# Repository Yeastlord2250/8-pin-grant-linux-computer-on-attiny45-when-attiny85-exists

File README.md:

# 8-pin-grant-linux-computer-on-attiny45-when-attiny85-exists
A stupid attempt at making a pcb with only 8-pin components using kicad, something I have never done, and also getting linux on an attiny 45, even though I could choose an attiny 85 instead.

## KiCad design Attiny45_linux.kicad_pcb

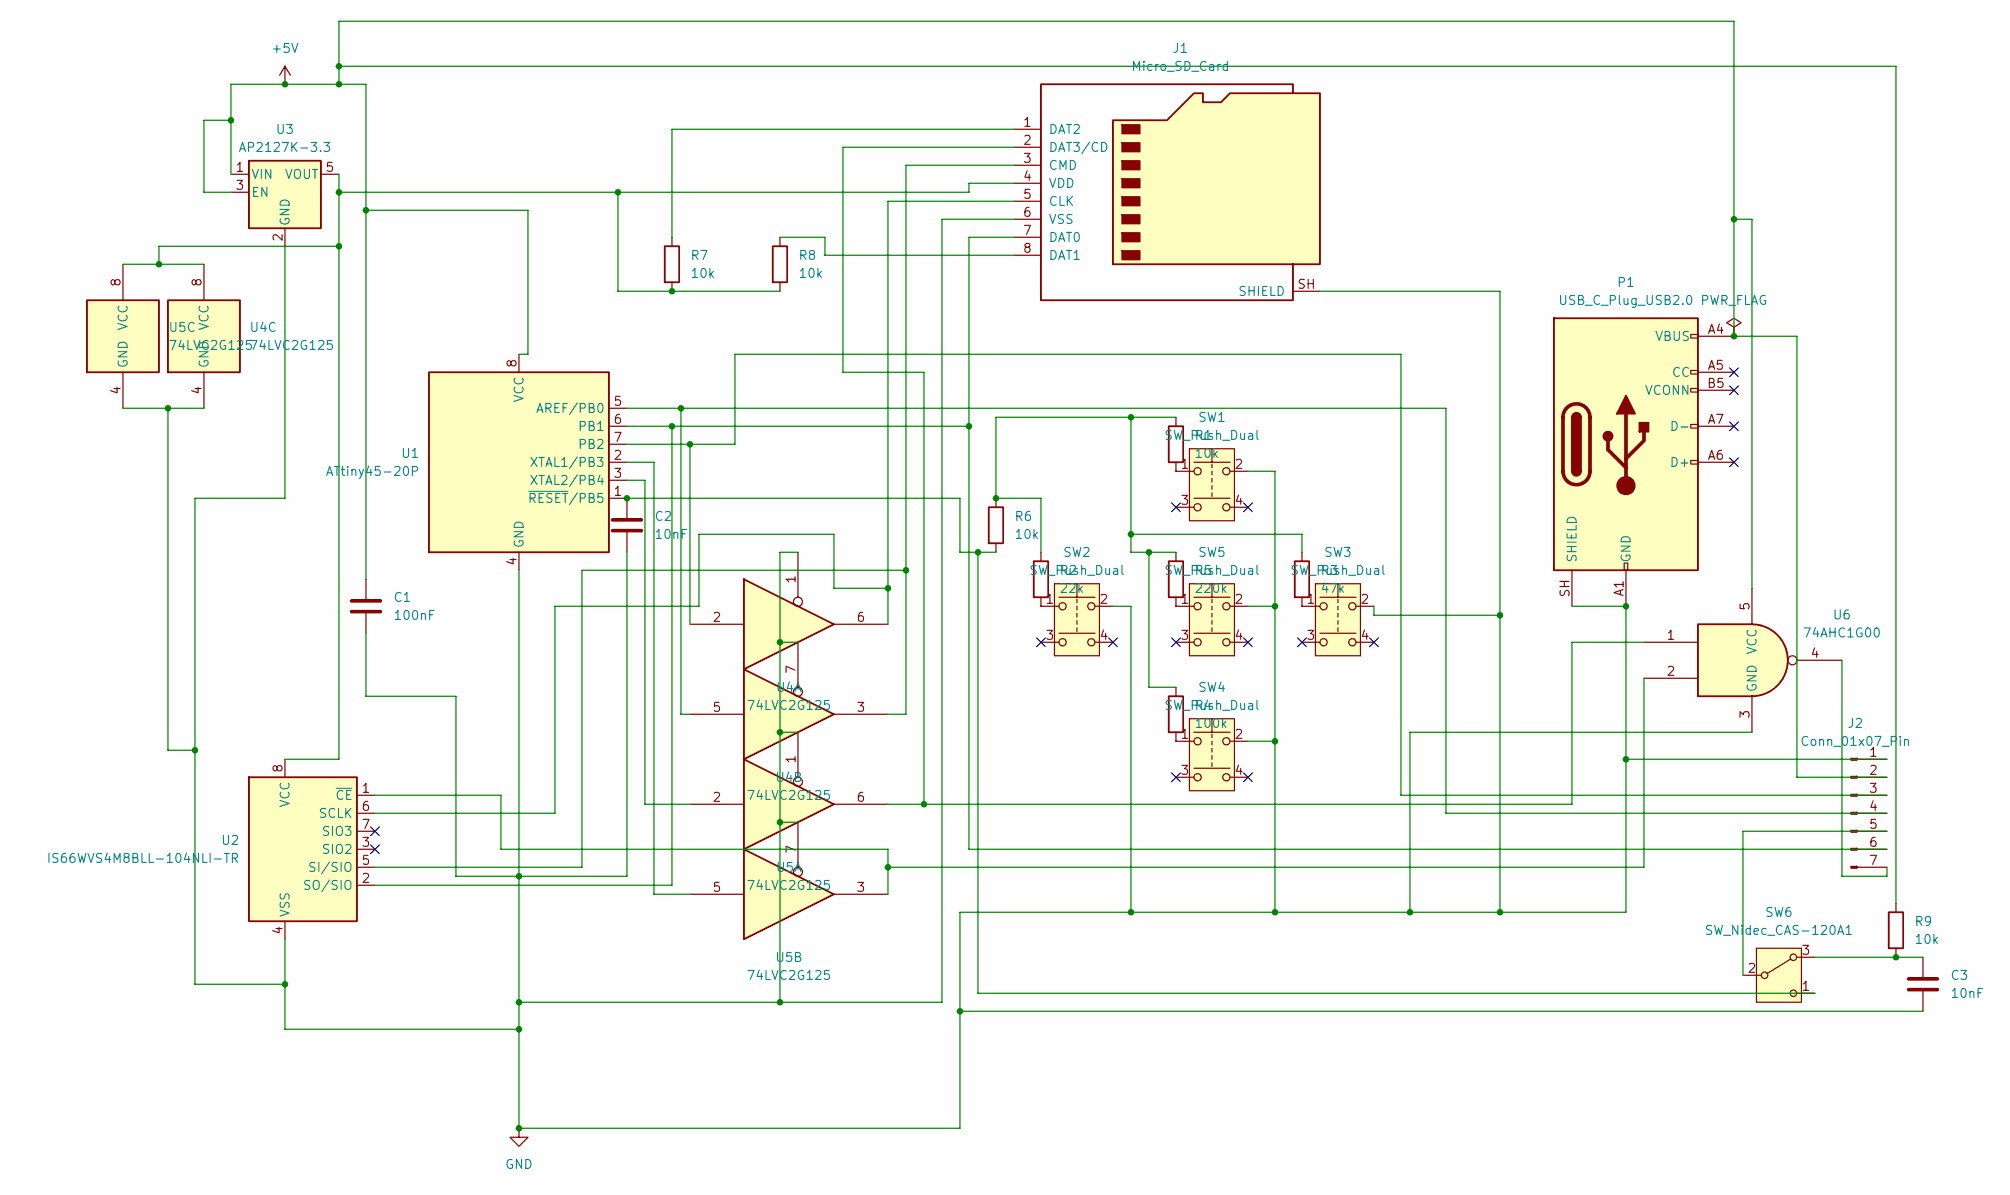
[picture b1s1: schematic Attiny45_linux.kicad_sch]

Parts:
C1: 100nF; C_0805_2012Metric
C2, C3: 10nF; C_0805_2012Metric
J1: Micro_SD_Card; microSD_HC_Hirose_DM3D-SF
J2: Conn_01x07_Pin; PinSocket_1x07_P2.54mm_Vertical
P1: USB_C_Plug_USB2.0; USB_C_Receptacle_GCT_USB4105-xx-A_16P_TopMnt_Horizontal
R1, R6, R7, R8, R9: 10k; R_01005_0402Metric
R2: 22k; R_01005_0402Metric
R3: 47k; R_01005_0402Metric
R4: 100k; R_01005_0402Metric
R5: 220k; R_01005_0402Metric
SW1, SW2, SW3, SW4, SW5: SW_Push_Dual; SW_Tactile_Straight_KSA0Axx1LFTR
SW6: SW_Nidec_CAS-120A1; SW_Slide_SPDT_Straight_CK_OS102011MS2Q
U1: ATtiny45-20P; DIP-8_W7.62mm
U2: IS66WVS4M8BLL-104NLI-TR; SOIC-8_3.9x4.9mm_P1.27mm; MPN IS66WVS4M8BLL-104NLI-TR; LCSC C17334768
U3: AP2127K-3.3; SOT-23-5
U4, U5: 74LVC2G125; VSSOP-8_3x3mm_P0.65mm
U6: 74AHC1G00; SOT-23-5

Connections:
+5V: C1.1, J2.2, P1.A4 (VBUS), P1.A9 (VBUS), P1.B4 (VBUS), P1.B9 (VBUS), R9.1, U1.8 (VCC), U3.1 (VIN), U3.3 (EN), U6.5 (VCC)
GND: C1.2, C2.2, C3.2, J1.6 (VSS), J1.SH (SHIELD), J2.1, P1.A1 (GND), P1.A12 (GND), P1.B1 (GND), P1.B12 (GND), P1.SH (SHIELD), SW1.2, SW2.2, SW3.2, SW4.2, SW5.2, U1.4 (GND), U2.4 (VSS), U3.2 (GND), U4.1, U4.4 (GND), U4.7, U5.1, U5.4 (GND), U5.7, U6.3 (GND)
unnamed: J1.5 (CLK), U2.6 (SCLK), U4.6
unnamed: J1.3 (CMD), U2.5 (SI/SIO), U4.3
unnamed: J1.7 (DAT0), J2.6, U1.6 (PB1), U2.2 (SO/SIO)
unnamed: J1.8 (DAT1), R8.1
unnamed: J1.1 (DAT2), R7.1
unnamed: J1.2 (DAT3/CD), U5.6, U6.1
unnamed: J1.4 (VDD), R7.2, R8.2, U2.8 (VCC), U3.5 (VOUT), U4.8 (VCC), U5.8 (VCC)
unnamed: J2.3, U1.7 (PB2), U4.2
unnamed: J2.4, U1.5 (AREF/PB0), U4.5
unnamed: J2.5, SW6.2 (B)
unnamed: J2.7, U6.4
unnamed: R1.1, R2.1, R3.1, R4.1, R5.1, R6.1
unnamed: R1.2, SW1.1
unnamed: R2.2, SW2.1
unnamed: R3.2, SW3.1
unnamed: R4.2, SW4.1
unnamed: R5.2, SW5.1
unnamed: C3.1, R9.2, SW6.3 (A)
unnamed: C2.1, R6.2, SW6.1 (C), U1.1 (~RESET/PB5)
unnamed: U1.2 (XTAL1/PB3), U5.5
unnamed: U1.3 (XTAL2/PB4), U5.2
unnamed: U2.1 (~CE), U5.3, U6.2

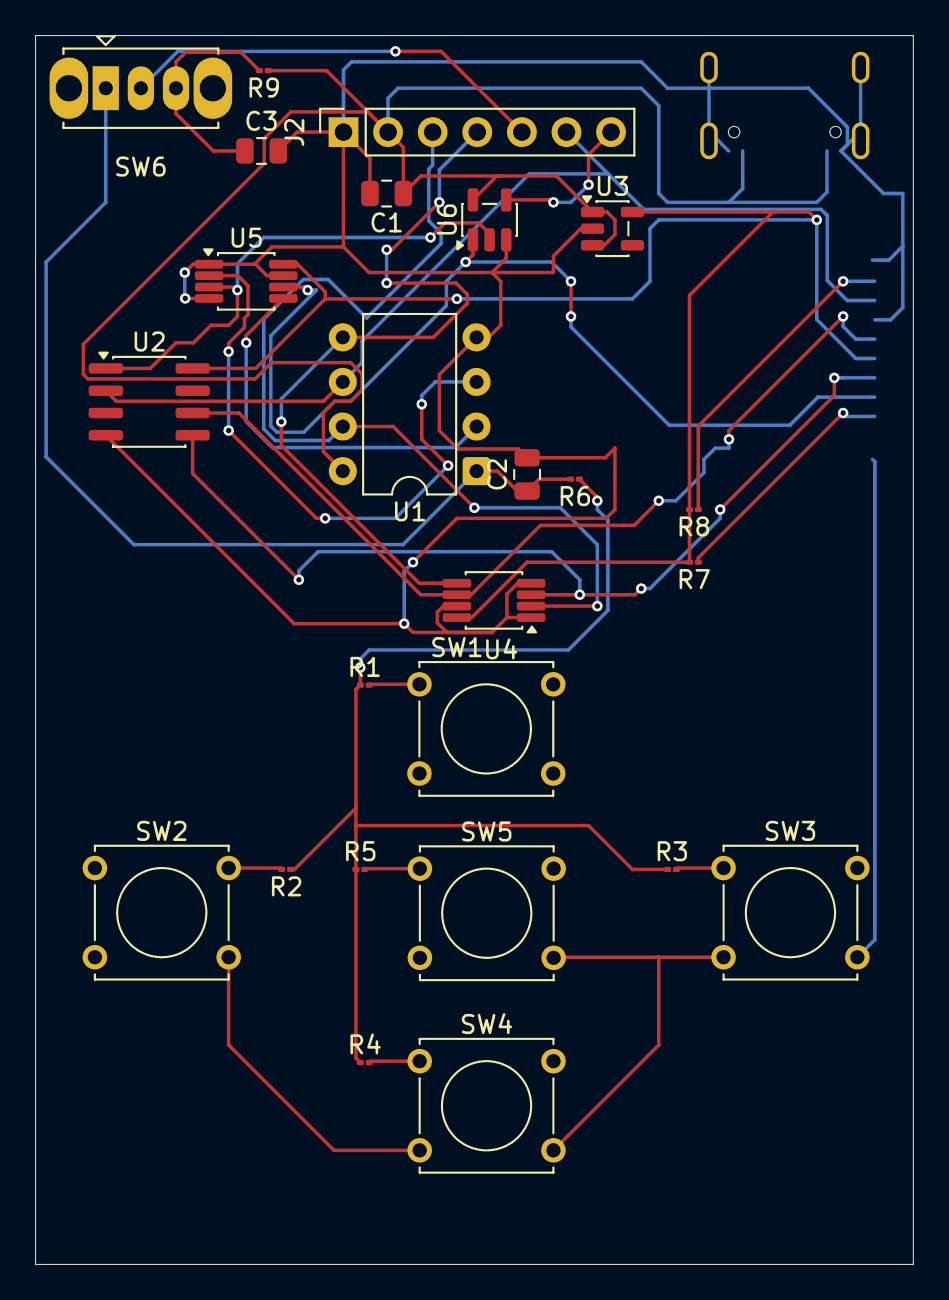
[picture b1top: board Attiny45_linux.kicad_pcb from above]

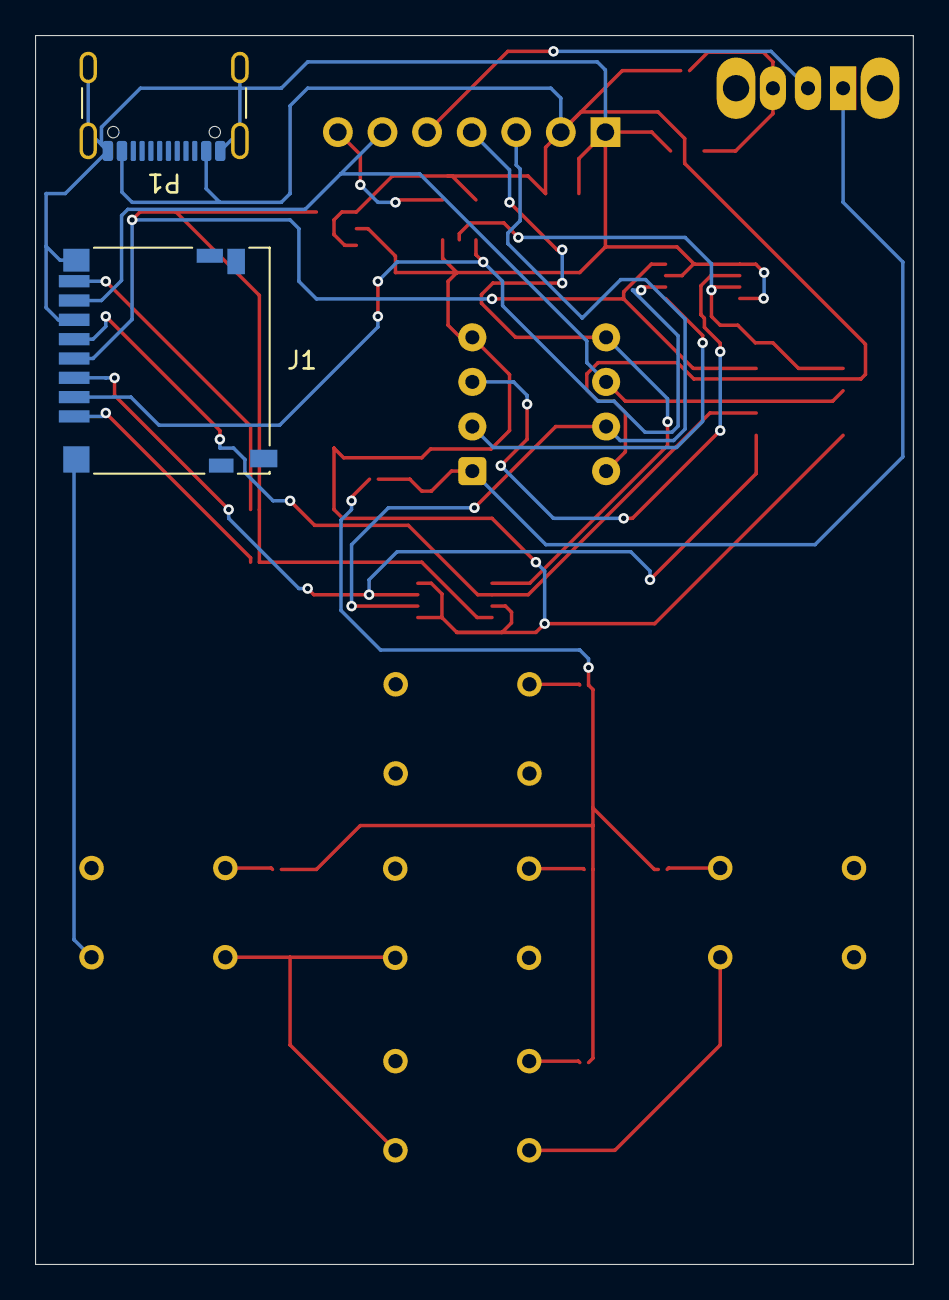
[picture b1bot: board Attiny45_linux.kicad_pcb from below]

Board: 2 copper layers, 50.0 x 70.0 mm, 27 parts (2 on the bottom side), 24 nets.
